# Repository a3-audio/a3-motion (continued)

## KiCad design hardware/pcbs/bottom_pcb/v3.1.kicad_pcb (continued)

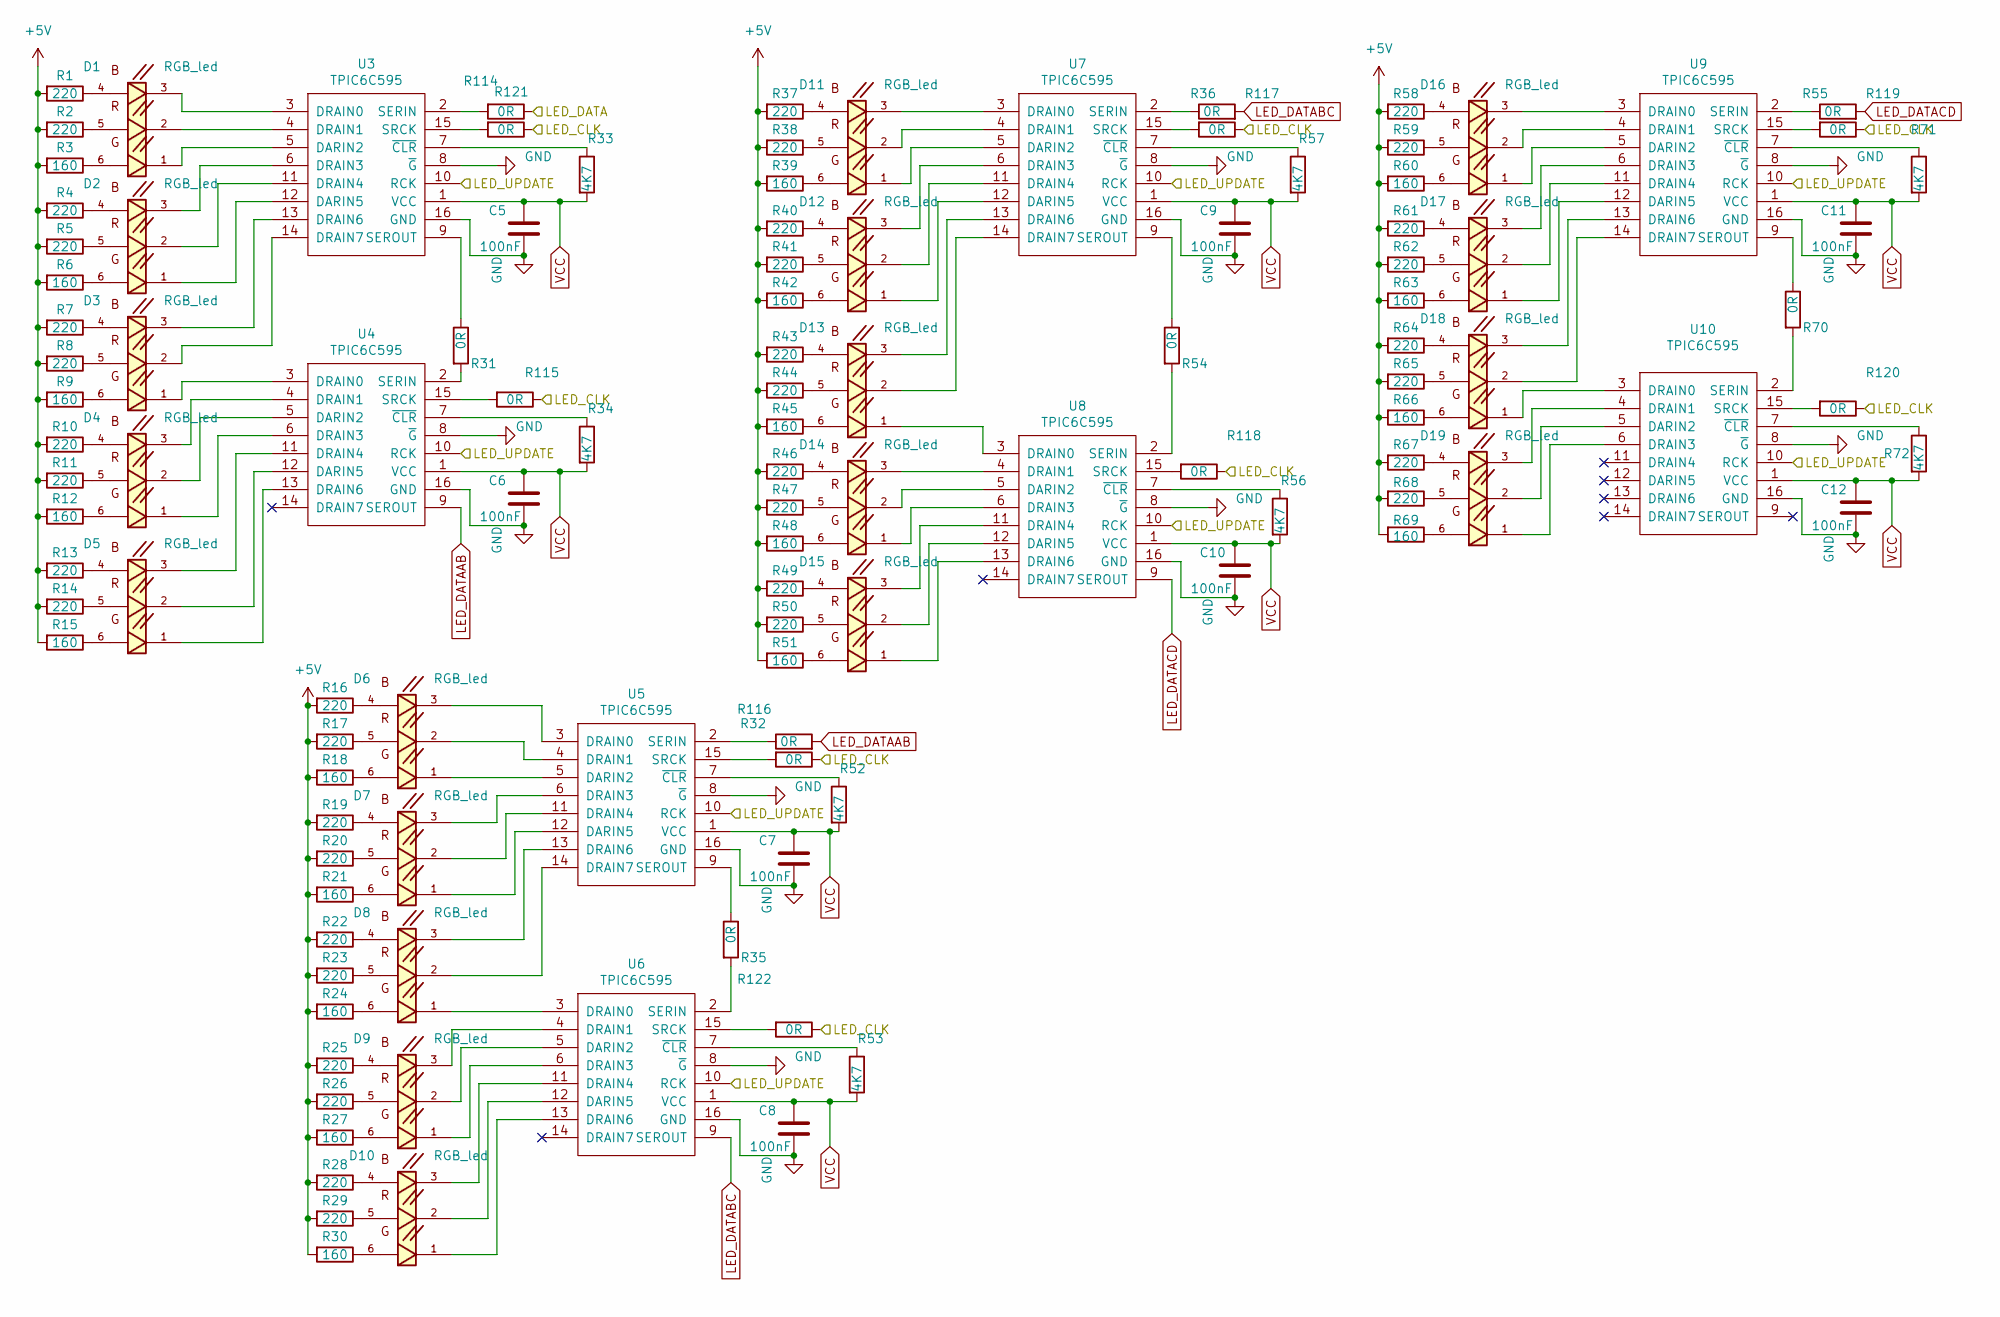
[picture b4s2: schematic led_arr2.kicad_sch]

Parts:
C5, C6, C7, C8, C9, C10, C11, C12: 100nF; C_1206_3216Metric_Pad1.33x1.80mm_HandSolder
D1, D2, D3, D4, D5, D6, D7, D8, D9, D10, D11, D12, D13, D14, D15, D16, D17, D18, D19: RGB_led; LED_QBLP679E-RGB; DigiKey_Part_Number 1516-1131-2-ND
R1, R2, R4, R5, R7, R8, R10, R11, R13, R14, R16, R17, R19, R20, R22, R23, R25, R26, R28, R29, R37, R38, R40, R41, R43, R44, R46, R47, R49, R50, R58, R59, R61, R62, R64, R65, R67, R68: 220; R_1206_3216Metric
R3, R6, R9, R12, R15, R18, R21, R24, R27, R30, R39, R42, R45, R48, R51, R60, R63, R66, R69: 160; R_1206_3216Metric
R31, R32, R35, R36, R54, R55, R70, R114, R115, R116, R117, R118, R119, R120, R121, R122: 0R; R_1206_3216Metric
R33, R34, R52, R53, R56, R57, R71, R72: 4K7; R_1206_3216Metric
U3, U4, U5, U6, U7, U8, U9, U10: TPIC6C595; SOIC-16_3.9x9.9mm_P1.27mm

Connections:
/LED/LED_CLK: R114.1, R115.1, R116.1, R117.1, R118.1, R119.1, R120.1, R122.1; also elsewhere on the board
/LED/LED_DATA: R121.1; also elsewhere on the board
/LED/LED_UPDATE: U3.10 (RCK), U4.10 (RCK), U5.10 (RCK), U6.10 (RCK), U7.10 (RCK), U8.10 (RCK), U9.10 (RCK), U10.10 (RCK); also elsewhere on the board
GND: C5.2, C6.2, C7.2, C8.2, C9.2, C10.2, C11.2, C12.2, U3.8 (~G), U3.16 (GND), U4.8 (~G), U4.16 (GND), U5.8 (~G), U5.16 (GND), U6.8 (~G), U6.16 (GND), U7.8 (~G), U7.16 (GND), U8.8 (~G), U8.16 (GND), U9.8 (~G), U9.16 (GND), U10.8 (~G), U10.16 (GND); also elsewhere on the board
LED_DATAAB: R32.2, U4.9 (SEROUT)
LED_DATABC: R36.2, U6.9 (SEROUT)
LED_DATACD: R55.2, U8.9 (SEROUT)
unnamed: D1.4, R1.1
unnamed: D1.5, R2.1
unnamed: D1.6, R3.1
unnamed: D2.4, R4.1
unnamed: D2.5, R5.1
unnamed: D2.6, R6.1
unnamed: D3.4, R7.1
unnamed: D3.5, R8.1
unnamed: D3.6, R9.1
unnamed: D4.4, R10.1
unnamed: D4.5, R11.1
unnamed: D4.6, R12.1
unnamed: D5.4, R13.1
unnamed: D5.5, R14.1
unnamed: D5.6, R15.1
unnamed: D6.4, R16.1
unnamed: D6.5, R17.1
unnamed: D6.6, R18.1
unnamed: D7.4, R19.1
unnamed: D7.5, R20.1
unnamed: D7.6, R21.1
unnamed: D8.4, R22.1
unnamed: D8.5, R23.1
unnamed: D8.6, R24.1
unnamed: D9.4, R25.1
unnamed: D9.5, R26.1
unnamed: D9.6, R27.1
unnamed: D10.4, R28.1
unnamed: D10.5, R29.1
unnamed: D10.6, R30.1
unnamed: D11.4, R37.1
unnamed: D11.5, R38.1
unnamed: D11.6, R39.1
unnamed: D12.4, R40.1
unnamed: D12.5, R41.1
unnamed: D12.6, R42.1
unnamed: D13.4, R43.1
unnamed: D13.5, R44.1
unnamed: D13.6, R45.1
unnamed: D14.4, R46.1
unnamed: D14.5, R47.1
unnamed: D14.6, R48.1
unnamed: D15.4, R49.1
unnamed: D15.5, R50.1
unnamed: D15.6, R51.1
unnamed: D16.4, R58.1
unnamed: D16.5, R59.1
unnamed: D16.6, R60.1
unnamed: D17.4, R61.1
unnamed: D17.5, R62.1
unnamed: D17.6, R63.1
unnamed: D18.4, R64.1
unnamed: D18.5, R65.1
unnamed: D18.6, R66.1
unnamed: D19.4, R67.1
unnamed: D19.5, R68.1
unnamed: D19.6, R69.1
unnamed: D1.1, U3.5 (DARIN2)
unnamed: D2.1, U3.12 (DARIN5)
unnamed: D1.3, U3.3 (DRAIN0)
unnamed: D1.2, U3.4 (DRAIN1)
unnamed: D2.3, U3.6 (DRAIN3)
unnamed: D2.2, U3.11 (DRAIN4)
unnamed: D3.3, U3.13 (DRAIN6)
unnamed: D3.2, U3.14 (DRAIN7)
unnamed: R121.2, U3.2 (SERIN)
unnamed: R31.1, U3.9 (SEROUT)
unnamed: R114.2, U3.15 (SRCK)
unnamed: R33.1, U3.7 (~CLR)
unnamed: D4.2, U4.5 (DARIN2)
unnamed: D5.2, U4.12 (DARIN5)
unnamed: D3.1, U4.3 (DRAIN0)
unnamed: D4.3, U4.4 (DRAIN1)
unnamed: D4.1, U4.6 (DRAIN3)
unnamed: D5.3, U4.11 (DRAIN4)
unnamed: D5.1, U4.13 (DRAIN6)
unnamed: R31.2, U4.2 (SERIN)
unnamed: R115.2, U4.15 (SRCK)
unnamed: R34.1, U4.7 (~CLR)
unnamed: D6.1, U5.5 (DARIN2)
unnamed: D7.1, U5.12 (DARIN5)
unnamed: D6.3, U5.3 (DRAIN0)
unnamed: D6.2, U5.4 (DRAIN1)
unnamed: D7.3, U5.6 (DRAIN3)
unnamed: D7.2, U5.11 (DRAIN4)
unnamed: D8.3, U5.13 (DRAIN6)
unnamed: D8.2, U5.14 (DRAIN7)
unnamed: R32.1, U5.2 (SERIN)
unnamed: R35.1, U5.9 (SEROUT)
unnamed: R116.2, U5.15 (SRCK)
unnamed: R52.1, U5.7 (~CLR)
unnamed: D9.2, U6.5 (DARIN2)
unnamed: D10.2, U6.12 (DARIN5)
unnamed: D8.1, U6.3 (DRAIN0)
unnamed: D9.3, U6.4 (DRAIN1)
unnamed: D9.1, U6.6 (DRAIN3)
unnamed: D10.3, U6.11 (DRAIN4)
unnamed: D10.1, U6.13 (DRAIN6)
unnamed: R35.2, U6.2 (SERIN)
unnamed: R122.2, U6.15 (SRCK)
unnamed: R53.1, U6.7 (~CLR)
unnamed: D11.1, U7.5 (DARIN2)
unnamed: D12.1, U7.12 (DARIN5)
unnamed: D11.3, U7.3 (DRAIN0)
unnamed: D11.2, U7.4 (DRAIN1)
unnamed: D12.3, U7.6 (DRAIN3)
unnamed: D12.2, U7.11 (DRAIN4)
unnamed: D13.3, U7.13 (DRAIN6)
unnamed: D13.2, U7.14 (DRAIN7)
unnamed: R36.1, U7.2 (SERIN)
unnamed: R54.1, U7.9 (SEROUT)
unnamed: R117.2, U7.15 (SRCK)
unnamed: R57.1, U7.7 (~CLR)
unnamed: D14.2, U8.5 (DARIN2)
unnamed: D15.2, U8.12 (DARIN5)
unnamed: D13.1, U8.3 (DRAIN0)
unnamed: D14.3, U8.4 (DRAIN1)
unnamed: D14.1, U8.6 (DRAIN3)
unnamed: D15.3, U8.11 (DRAIN4)
unnamed: D15.1, U8.13 (DRAIN6)
unnamed: R54.2, U8.2 (SERIN)
unnamed: R118.2, U8.15 (SRCK)
unnamed: R56.1, U8.7 (~CLR)
unnamed: D16.1, U9.5 (DARIN2)
unnamed: D17.1, U9.12 (DARIN5)
unnamed: D16.3, U9.3 (DRAIN0)
unnamed: D16.2, U9.4 (DRAIN1)
unnamed: D17.3, U9.6 (DRAIN3)
unnamed: D17.2, U9.11 (DRAIN4)
unnamed: D18.3, U9.13 (DRAIN6)
unnamed: D18.2, U9.14 (DRAIN7)
unnamed: R55.1, U9.2 (SERIN)
unnamed: R70.1, U9.9 (SEROUT)
unnamed: R119.2, U9.15 (SRCK)
unnamed: R71.1, U9.7 (~CLR)
unnamed: D19.2, U10.5 (DARIN2)
unnamed: D18.1, U10.3 (DRAIN0)
unnamed: D19.3, U10.4 (DRAIN1)
unnamed: D19.1, U10.6 (DRAIN3)
unnamed: R70.2, U10.2 (SERIN)
unnamed: R120.2, U10.15 (SRCK)
unnamed: R72.1, U10.7 (~CLR)
VCC: C5.1, C6.1, C7.1, C8.1, C9.1, C10.1, C11.1, C12.1, R1.2, R2.2, R3.2, R4.2, R5.2, R6.2, R7.2, R8.2, R9.2, R10.2, R11.2, R12.2, R13.2, R14.2, R15.2, R16.2, R17.2, R18.2, R19.2, R20.2, R21.2, R22.2, R23.2, R24.2, R25.2, R26.2, R27.2, R28.2, R29.2, R30.2, R33.2, R34.2, R37.2, R38.2, R39.2, R40.2, R41.2, R42.2, R43.2, R44.2, R45.2, R46.2, R47.2, R48.2, R49.2, R50.2, R51.2, R52.2, R53.2, R56.2, R57.2, R58.2, R59.2, R60.2, R61.2, R62.2, R63.2, R64.2, R65.2, R66.2, R67.2, R68.2, R69.2, R71.2, R72.2, U3.1 (VCC), U4.1 (VCC), U5.1 (VCC), U6.1 (VCC), U7.1 (VCC), U8.1 (VCC), U9.1 (VCC), U10.1 (VCC); also elsewhere on the board

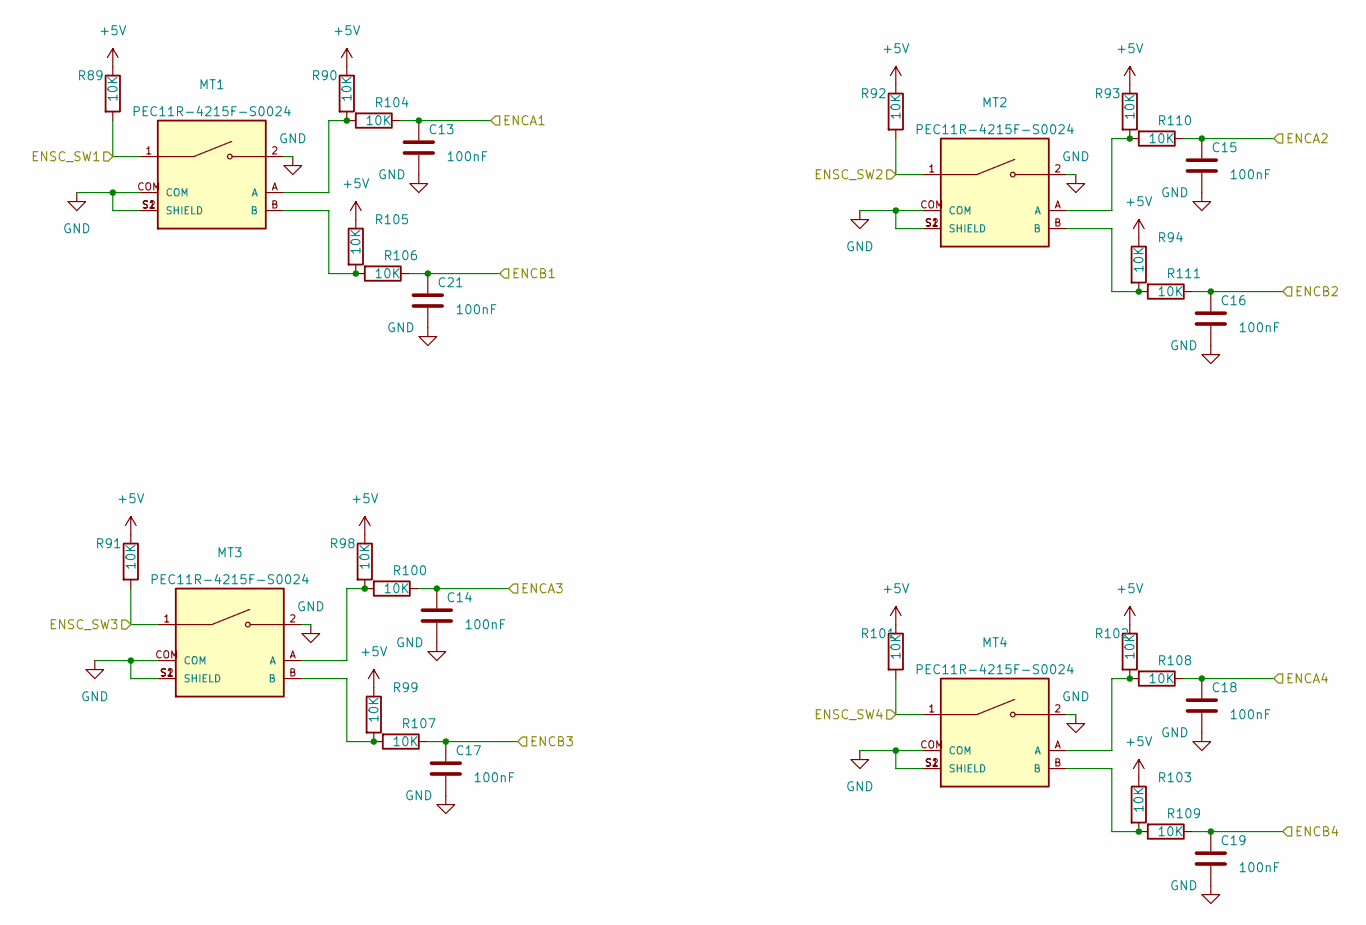
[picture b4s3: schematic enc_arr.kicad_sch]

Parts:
C13, C14, C15, C16, C17, C18, C19, C21: 100nF; C_1206_3216Metric_Pad1.33x1.80mm_HandSolder
MT1, MT2, MT3, MT4: PEC11R-4215F-S0024; XDCR_PEC11R-4215F-S0024; PARTREV Rev. 09/19; DigiKey_Part_Number PEC11R-4215F-S0024-ND
R89, R90, R91, R92, R93, R94, R98, R99, R100, R101, R102, R103, R104, R105, R106, R107, R108, R109, R110, R111: 10K; R_1206_3216Metric

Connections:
EA1: C13.1, R104.1; also elsewhere on the board
EA2: C15.1, R110.1; also elsewhere on the board
EA3: C14.1, R100.1; also elsewhere on the board
EA4: C18.1, R108.1; also elsewhere on the board
EB1: C21.1, R106.1; also elsewhere on the board
EB2: C16.1, R111.1; also elsewhere on the board
EB3: C17.1, R107.1; also elsewhere on the board
EB4: C19.1, R109.1; also elsewhere on the board
ES1: MT1.1, R89.2; also elsewhere on the board
ES2: MT2.1, R92.2; also elsewhere on the board
ES3: MT3.1, R91.2; also elsewhere on the board
ES4: MT4.1, R101.2; also elsewhere on the board
GND: C13.2, C14.2, C15.2, C16.2, C17.2, C18.2, C19.2, C21.2, MT1.2, MT1.COM, MT1.S1 (SHIELD), MT1.S2 (SHIELD), MT2.2, MT2.COM, MT2.S1 (SHIELD), MT2.S2 (SHIELD), MT3.2, MT3.COM, MT3.S1 (SHIELD), MT3.S2 (SHIELD), MT4.2, MT4.COM, MT4.S1 (SHIELD), MT4.S2 (SHIELD); also elsewhere on the board
unnamed: MT1.A, R90.2, R104.2
unnamed: MT1.B, R105.2, R106.2
unnamed: MT2.A, R93.2, R110.2
unnamed: MT2.B, R94.2, R111.2
unnamed: MT3.A, R98.2, R100.2
unnamed: MT3.B, R99.2, R107.2
unnamed: MT4.A, R102.2, R108.2
unnamed: MT4.B, R103.2, R109.2
VCC: R89.1, R90.1, R91.1, R92.1, R93.1, R94.1, R98.1, R99.1, R101.1, R102.1, R103.1, R105.1; also elsewhere on the board

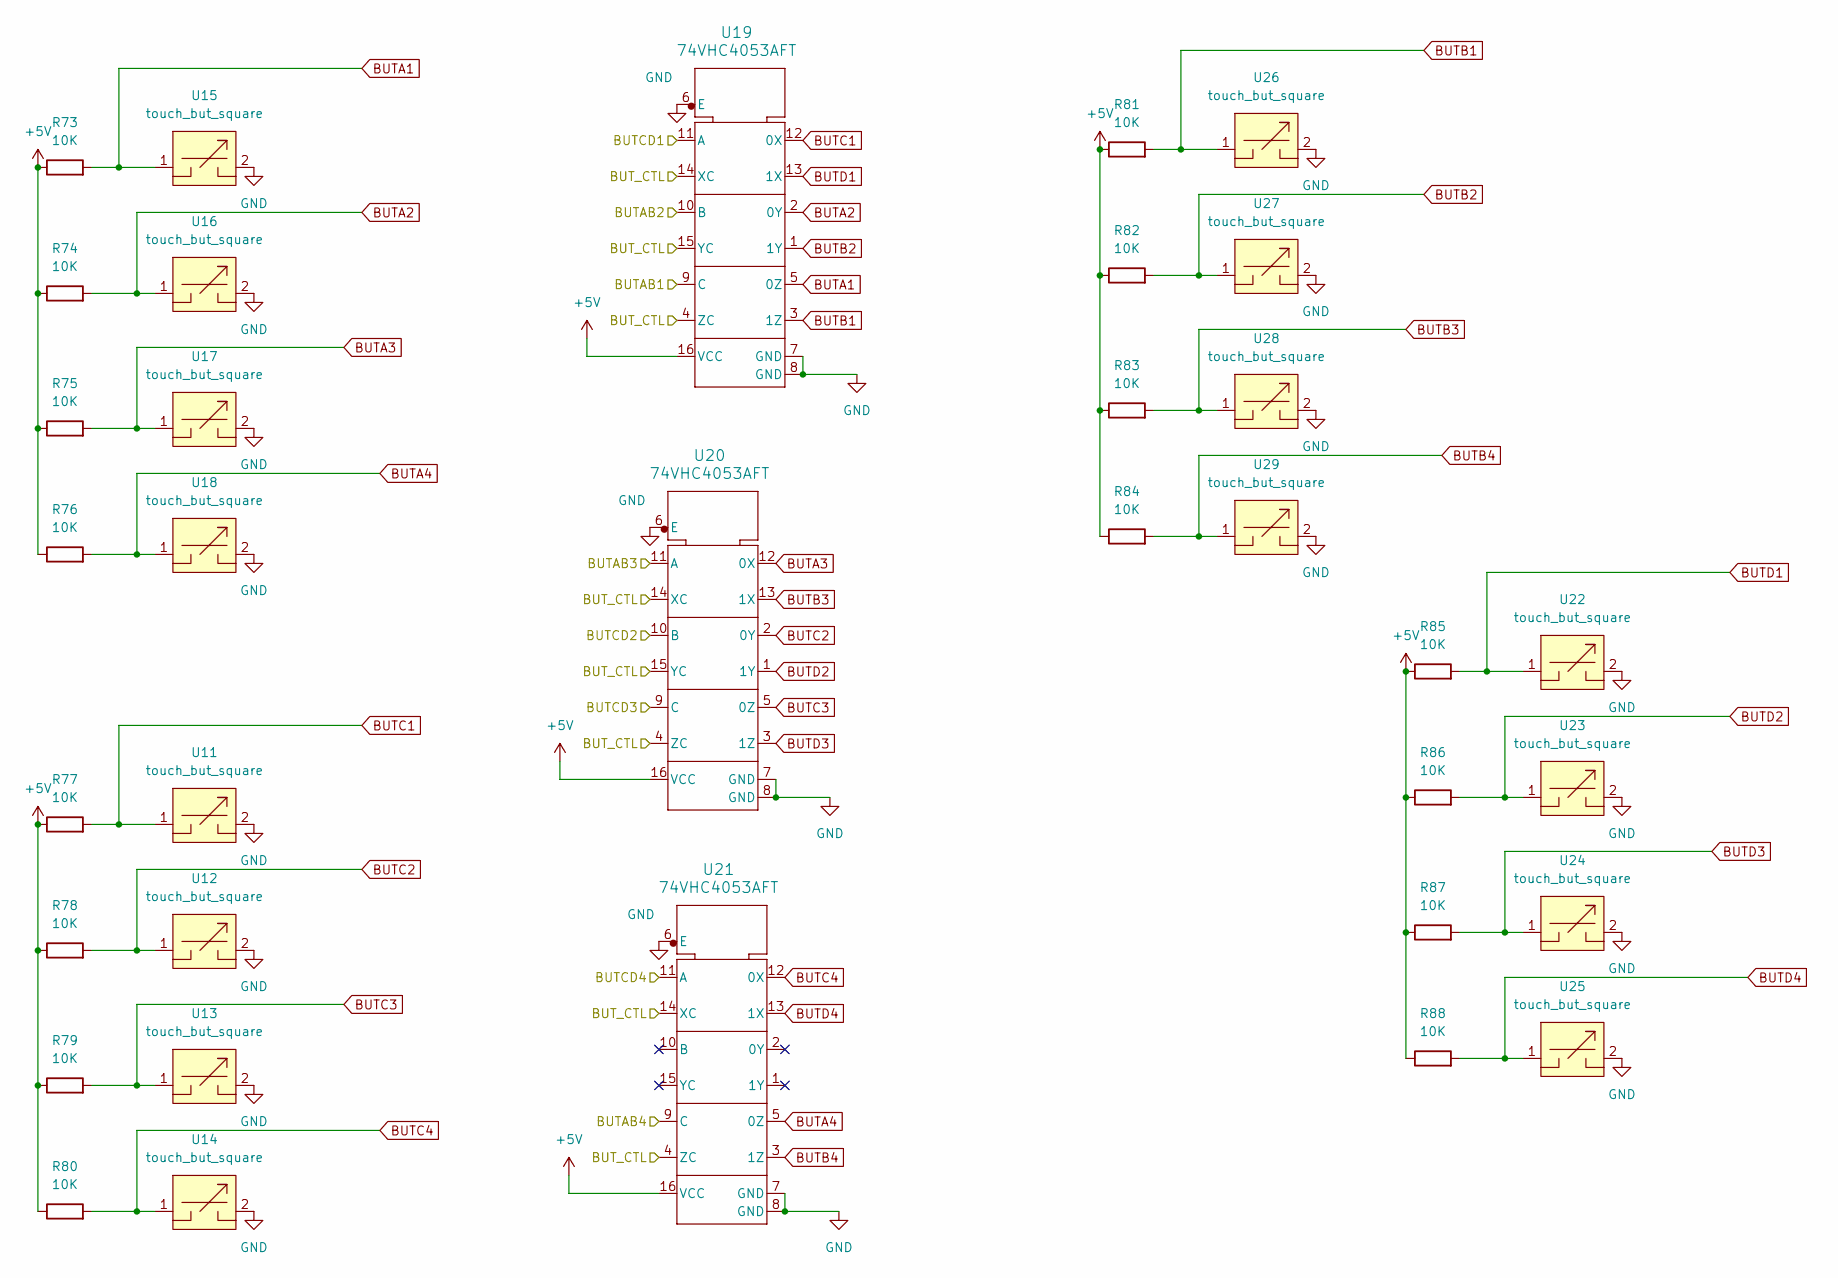
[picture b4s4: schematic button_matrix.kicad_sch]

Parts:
R73, R74, R75, R76, R77, R78, R79, R80, R81, R82, R83, R84, R85, R86, R87, R88: 10K; R_1206_3216Metric
U11, U12, U13, U14, U15, U16, U17, U18, U22, U23, U24, U25, U26, U27, U28, U29: touch_but_square; But_Velo_Rec_1
U19, U20, U21: 74VHC4053AFT; 74vhc4053aft

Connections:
BAB1: U19.9 (C); also elsewhere on the board
BAB2: U19.10 (B); also elsewhere on the board
BAB3: U20.11 (A); also elsewhere on the board
BAB4: U21.9 (C); also elsewhere on the board
BCD1: U19.11 (A); also elsewhere on the board
BCD2: U20.10 (B); also elsewhere on the board
BCD3: U20.9 (C); also elsewhere on the board
BCD4: U21.11 (A); also elsewhere on the board
BCNT: U19.4 (ZC), U19.14 (XC), U19.15 (YC), U20.4 (ZC), U20.14 (XC), U20.15 (YC), U21.4 (ZC), U21.14 (XC); also elsewhere on the board
BUTA1: R73.2, U15.1, U19.5 (0Z)
BUTA2: R74.2, U16.1, U19.2 (0Y)
BUTA3: R75.2, U17.1, U20.12 (0X)
BUTA4: R76.2, U18.1, U21.5 (0Z)
BUTB1: R81.2, U19.3 (1Z), U26.1
BUTB2: R82.2, U19.1 (1Y), U27.1
BUTB3: R83.2, U20.13 (1X), U28.1
BUTB4: R84.2, U21.3 (1Z), U29.1
BUTC1: R77.2, U11.1, U19.12 (0X)
BUTC2: R78.2, U12.1, U20.2 (0Y)
BUTC3: R79.2, U13.1, U20.5 (0Z)
BUTC4: R80.2, U14.1, U21.12 (0X)
BUTD1: R85.2, U19.13 (1X), U22.1
BUTD2: R86.2, U20.1 (1Y), U23.1
BUTD3: R87.2, U20.3 (1Z), U24.1
BUTD4: R88.2, U21.13 (1X), U25.1
GND: U11.2, U12.2, U13.2, U14.2, U15.2, U16.2, U17.2, U18.2, U19.6 (E), U19.7 (GND), U19.8 (GND), U20.6 (E), U20.7 (GND), U20.8 (GND), U21.6 (E), U21.7 (GND), U21.8 (GND), U22.2, U23.2, U24.2, U25.2, U26.2, U27.2, U28.2, U29.2; also elsewhere on the board
VCC: R73.1, R74.1, R75.1, R76.1, R77.1, R78.1, R79.1, R80.1, R81.1, R82.1, R83.1, R84.1, R85.1, R86.1, R87.1, R88.1, U19.16 (VCC), U20.16 (VCC), U21.16 (VCC); also elsewhere on the board

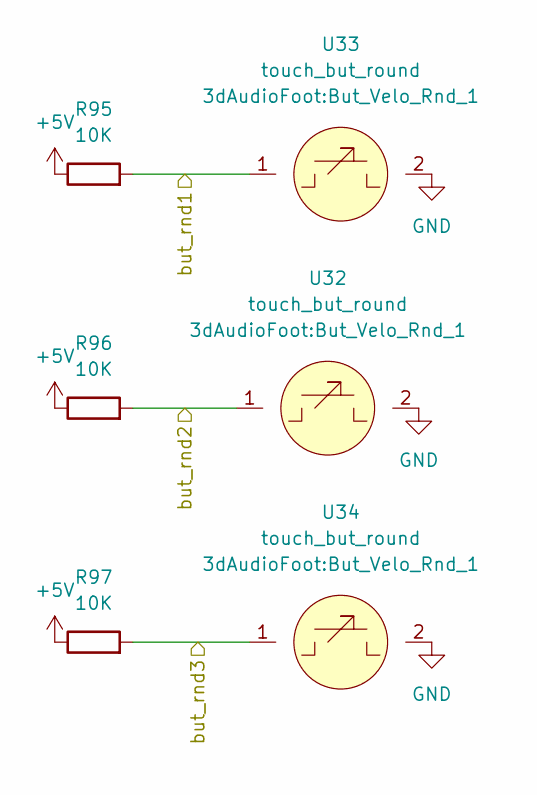
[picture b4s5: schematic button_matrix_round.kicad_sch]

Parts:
R95, R96, R97: 10K; R_1206_3216Metric
U32, U33, U34: touch_but_round; But_Velo_Rnd_1

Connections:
BR1: R95.2, U33.1; also elsewhere on the board
BR2: R96.2, U32.1; also elsewhere on the board
BR3: R97.2, U34.1; also elsewhere on the board
GND: U32.2, U33.2, U34.2; also elsewhere on the board
VCC: R95.1, R96.1, R97.1; also elsewhere on the board

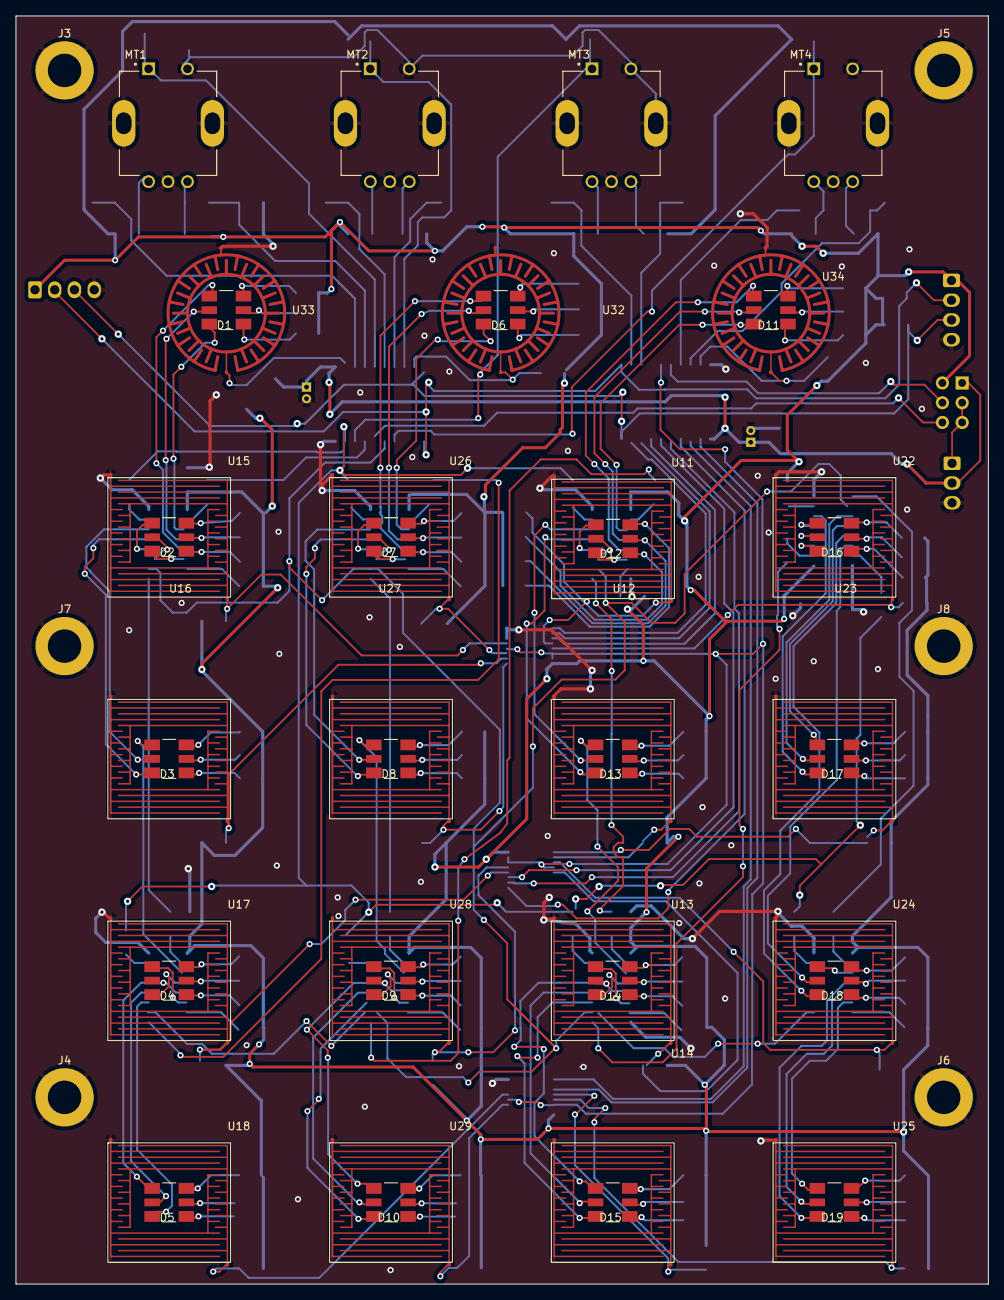
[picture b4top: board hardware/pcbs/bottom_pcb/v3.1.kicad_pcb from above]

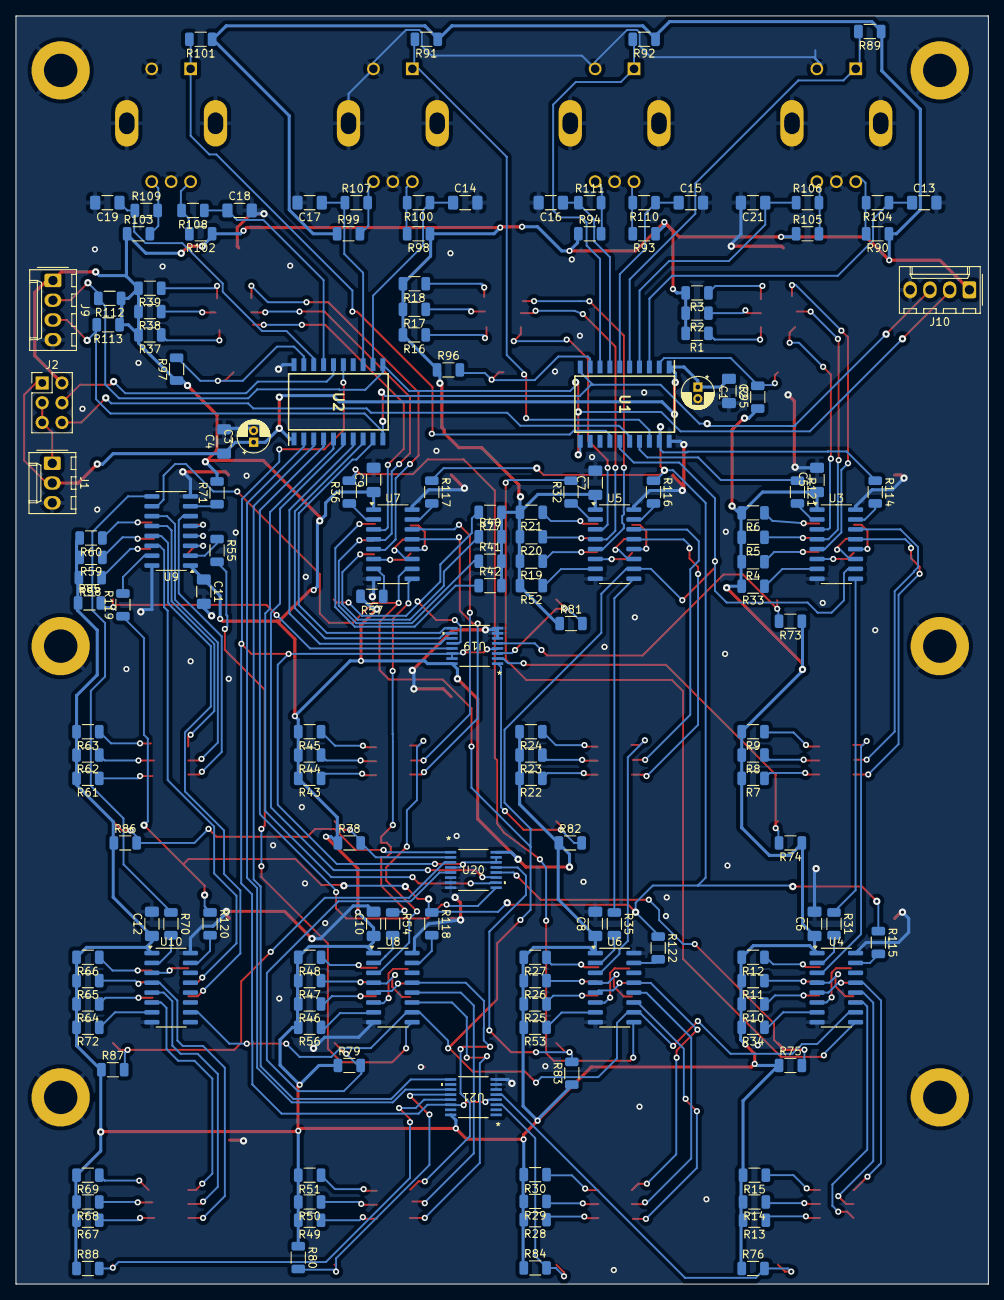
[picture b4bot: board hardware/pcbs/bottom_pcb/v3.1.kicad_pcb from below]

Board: 2 copper layers, 125.0 x 163.0 mm, 207 parts (159 on the bottom side), 204 nets.

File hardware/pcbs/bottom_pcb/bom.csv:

"Reference","Value","Datasheet","Footprint","Qty","DNP"
"C1,C3","10uF","~","Capacitor_THT:CP_Radial_D4.0mm_P1.50mm","2",""
"C2,C4,C5,C6,C7,C8,C9,C10,C11,C12,C13,C14,C15,C16,C17,C18,C19,C21","100nF","~","Capacitor_SMD:C_1206_3216Metric_Pad1.33x1.80mm_HandSolder","18",""
"D1,D2,D3,D4,D5,D6,D7,D8,D9,D10,D11,D12,D13,D14,D15,D16,D17,D18,D19","RGB_led","https://www.digikey.de/de/products/detail/qt-brightek-qtb/QB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","3dAudioFoot:LED_QBLP679E-RGB","19",""
"J1","Programming Connector","~","3dAudioFoot:Molex_KK-254_AE-6410-03A_1x03_P2.54mm_Vertical","1",""
"J2","Jumper","~","Connector_PinHeader_2.54mm:PinHeader_2x03_P2.54mm_Vertical","1",""
"J3,J4,J5,J6,J7,J8","mount_hole","~","MountingHole:MountingHole_4.3mm_M4_DIN965_Pad","6",""
"J9","Main Com","~","Connector_Molex:Molex_KK-254_AE-6410-04A_1x04_P2.54mm_Vertical","1",""
"J10","Sec Com","~","Connector_Molex:Molex_KK-254_AE-6410-04A_1x04_P2.54mm_Vertical","1",""
"MT1,MT2,MT3,MT4","PEC11R-4215F-S0024","","3dAudioFoot:XDCR_PEC11R-4215F-S0024","4",""
"R1,R2,R4,R5,R7,R8,R10,R11,R13,R14,R16,R17,R19,R20,R22,R23,R25,R26,R28,R29,R37,R38,R40,R41,R43,R44,R46,R47,R49,R50,R58,R59,R61,R62,R64,R65,R67,R68","220","~","Resistor_SMD:R_1206_3216Metric","38",""
"R3,R6,R9,R12,R15,R18,R21,R24,R27,R30,R39,R42,R45,R48,R51,R60,R63,R66,R69","160","~","Resistor_SMD:R_1206_3216Metric","19",""
"R31,R32,R35,R36,R54,R55,R70,R114,R115,R116,R117,R118,R119,R120,R121,R122","0R","~","Resistor_SMD:R_1206_3216Metric","16",""
"R33,R34,R52,R53,R56,R57,R71,R72","4K7","~","Resistor_SMD:R_1206_3216Metric","8",""
"R73,R74,R75,R76,R77,R78,R79,R80,R81,R82,R83,R84,R85,R86,R87,R88,R89,R90,R91,R92,R93,R94,R95,R96,R97,R98,R99,R100,R101,R102,R103,R104,R105,R106,R107,R108,R109,R110,R111,R112,R113","10K","~","Resistor_SMD:R_1206_3216Metric","41",""
"U1,U2","ATtiny1626","","3dAudioFoot:attiny1626","2",""
"U3,U4,U5,U6,U7,U8,U9,U10","TPIC6C595","https://www.mouser.ph/datasheet/2/389/cd00020664-1796042.pdf","Package_SO:SOIC-16_3.9x9.9mm_P1.27mm","8",""
"U11,U12,U13,U14,U15,U16,U17,U18,U22,U23,U24,U25,U26,U27,U28,U29","touch_but_square","","3dAudioFoot:But_Velo_Rec_1","16",""
"U19,U20,U21","74VHC4053AFT","74VHC4053AFT","3dAudioFoot:74vhc4053aft","3",""
"U32,U33,U34","touch_but_round","","3dAudioFoot:But_Velo_Rnd_1","3",""

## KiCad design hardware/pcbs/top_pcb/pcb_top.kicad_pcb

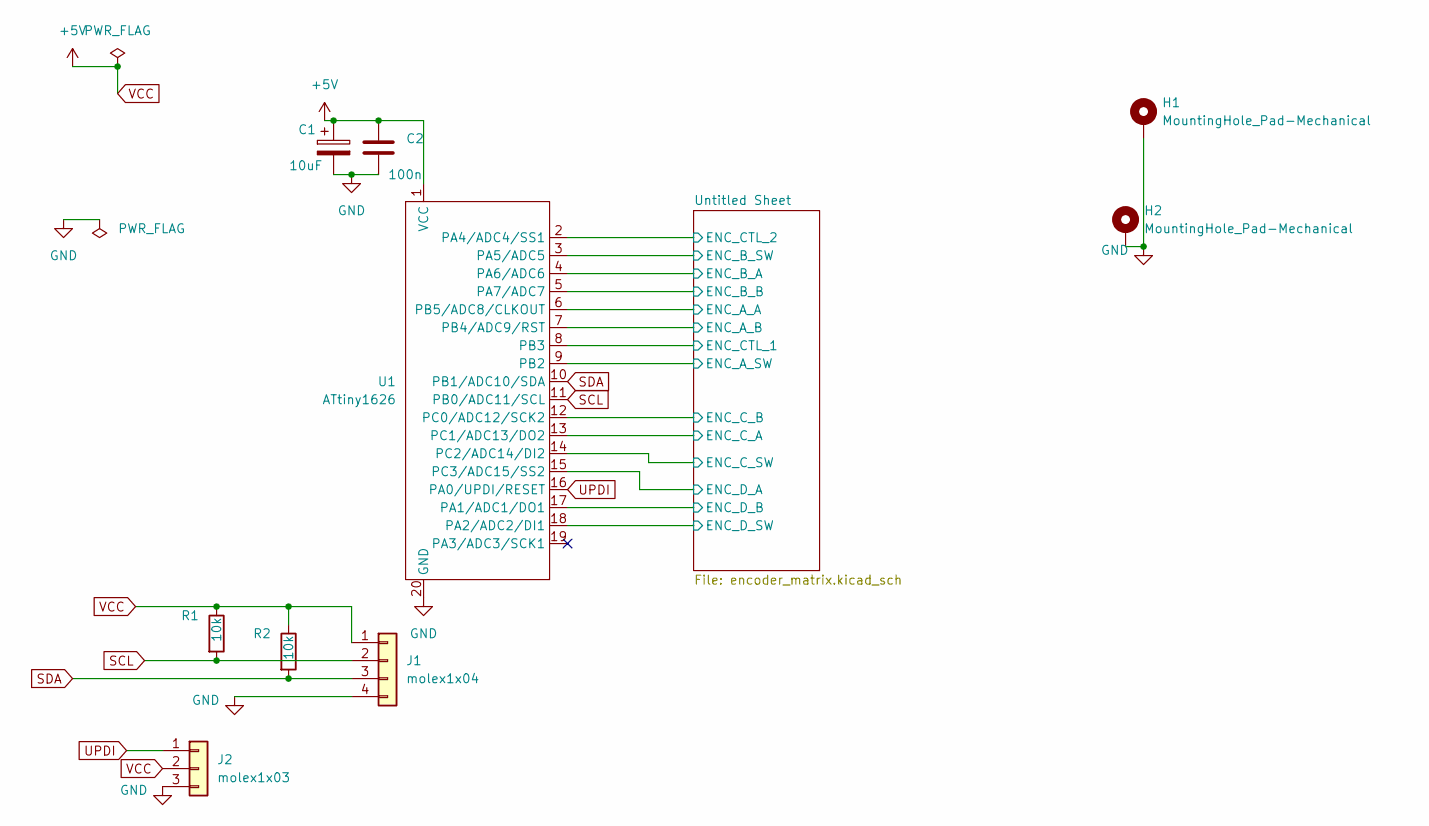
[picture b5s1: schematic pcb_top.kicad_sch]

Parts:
C1: 10uF; CP_Radial_D4.0mm_P1.50mm
C2: 100n; C_1206_3216Metric_Pad1.33x1.80mm_HandSolder
H1, H2: MountingHole_Pad-Mechanical; MountingHole_4.3mm_M4_DIN965_Pad
J1: molex1x04; Molex_KK-254_AE-6410-04A_1x04_P2.54mm_Vertical
J2: molex1x03; Molex_KK-254_AE-6410-03A_1x03_P2.54mm_Vertical
R1, R2: 10k; R_1206_3216Metric_Pad1.30x1.75mm_HandSolder
U1: ATtiny1626; attiny1626

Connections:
/Untitled Sheet/ENC_A_A: U1.6 (PB5/ADC8/CLKOUT); also elsewhere on the board
/Untitled Sheet/ENC_A_B: U1.7 (PB4/ADC9/RST); also elsewhere on the board
/Untitled Sheet/ENC_A_SW: U1.9 (PB2); also elsewhere on the board
/Untitled Sheet/ENC_B_A: U1.4 (PA6/ADC6); also elsewhere on the board
/Untitled Sheet/ENC_B_B: U1.5 (PA7/ADC7); also elsewhere on the board
/Untitled Sheet/ENC_B_SW: U1.3 (PA5/ADC5); also elsewhere on the board
/Untitled Sheet/ENC_CTL_1: U1.8 (PB3); also elsewhere on the board
/Untitled Sheet/ENC_CTL_2: U1.2 (PA4/ADC4/SS1); also elsewhere on the board
/Untitled Sheet/ENC_C_A: U1.13 (PC1/ADC13/DO2); also elsewhere on the board
/Untitled Sheet/ENC_C_B: U1.12 (PC0/ADC12/SCK2); also elsewhere on the board
/Untitled Sheet/ENC_C_SW: U1.14 (PC2/ADC14/DI2); also elsewhere on the board
/Untitled Sheet/ENC_D_A: U1.15 (PC3/ADC15/SS2); also elsewhere on the board
/Untitled Sheet/ENC_D_B: U1.17 (PA1/ADC1/DO1); also elsewhere on the board
/Untitled Sheet/ENC_D_SW: U1.18 (PA2/ADC2/DI1); also elsewhere on the board
GND: C1.2, C2.2, H1.1, H2.1, J1.4, J2.3, U1.20 (GND); also elsewhere on the board
SCL: J1.2, R1.2, U1.11 (PB0/ADC11/SCL)
SDA: J1.3, R2.2, U1.10 (PB1/ADC10/SDA)
UPDI: J2.1, U1.16 (PA0/UPDI/RESET)
VCC: C1.1, C2.1, J1.1, J2.2, R1.1, R2.1, U1.1 (VCC); also elsewhere on the board
